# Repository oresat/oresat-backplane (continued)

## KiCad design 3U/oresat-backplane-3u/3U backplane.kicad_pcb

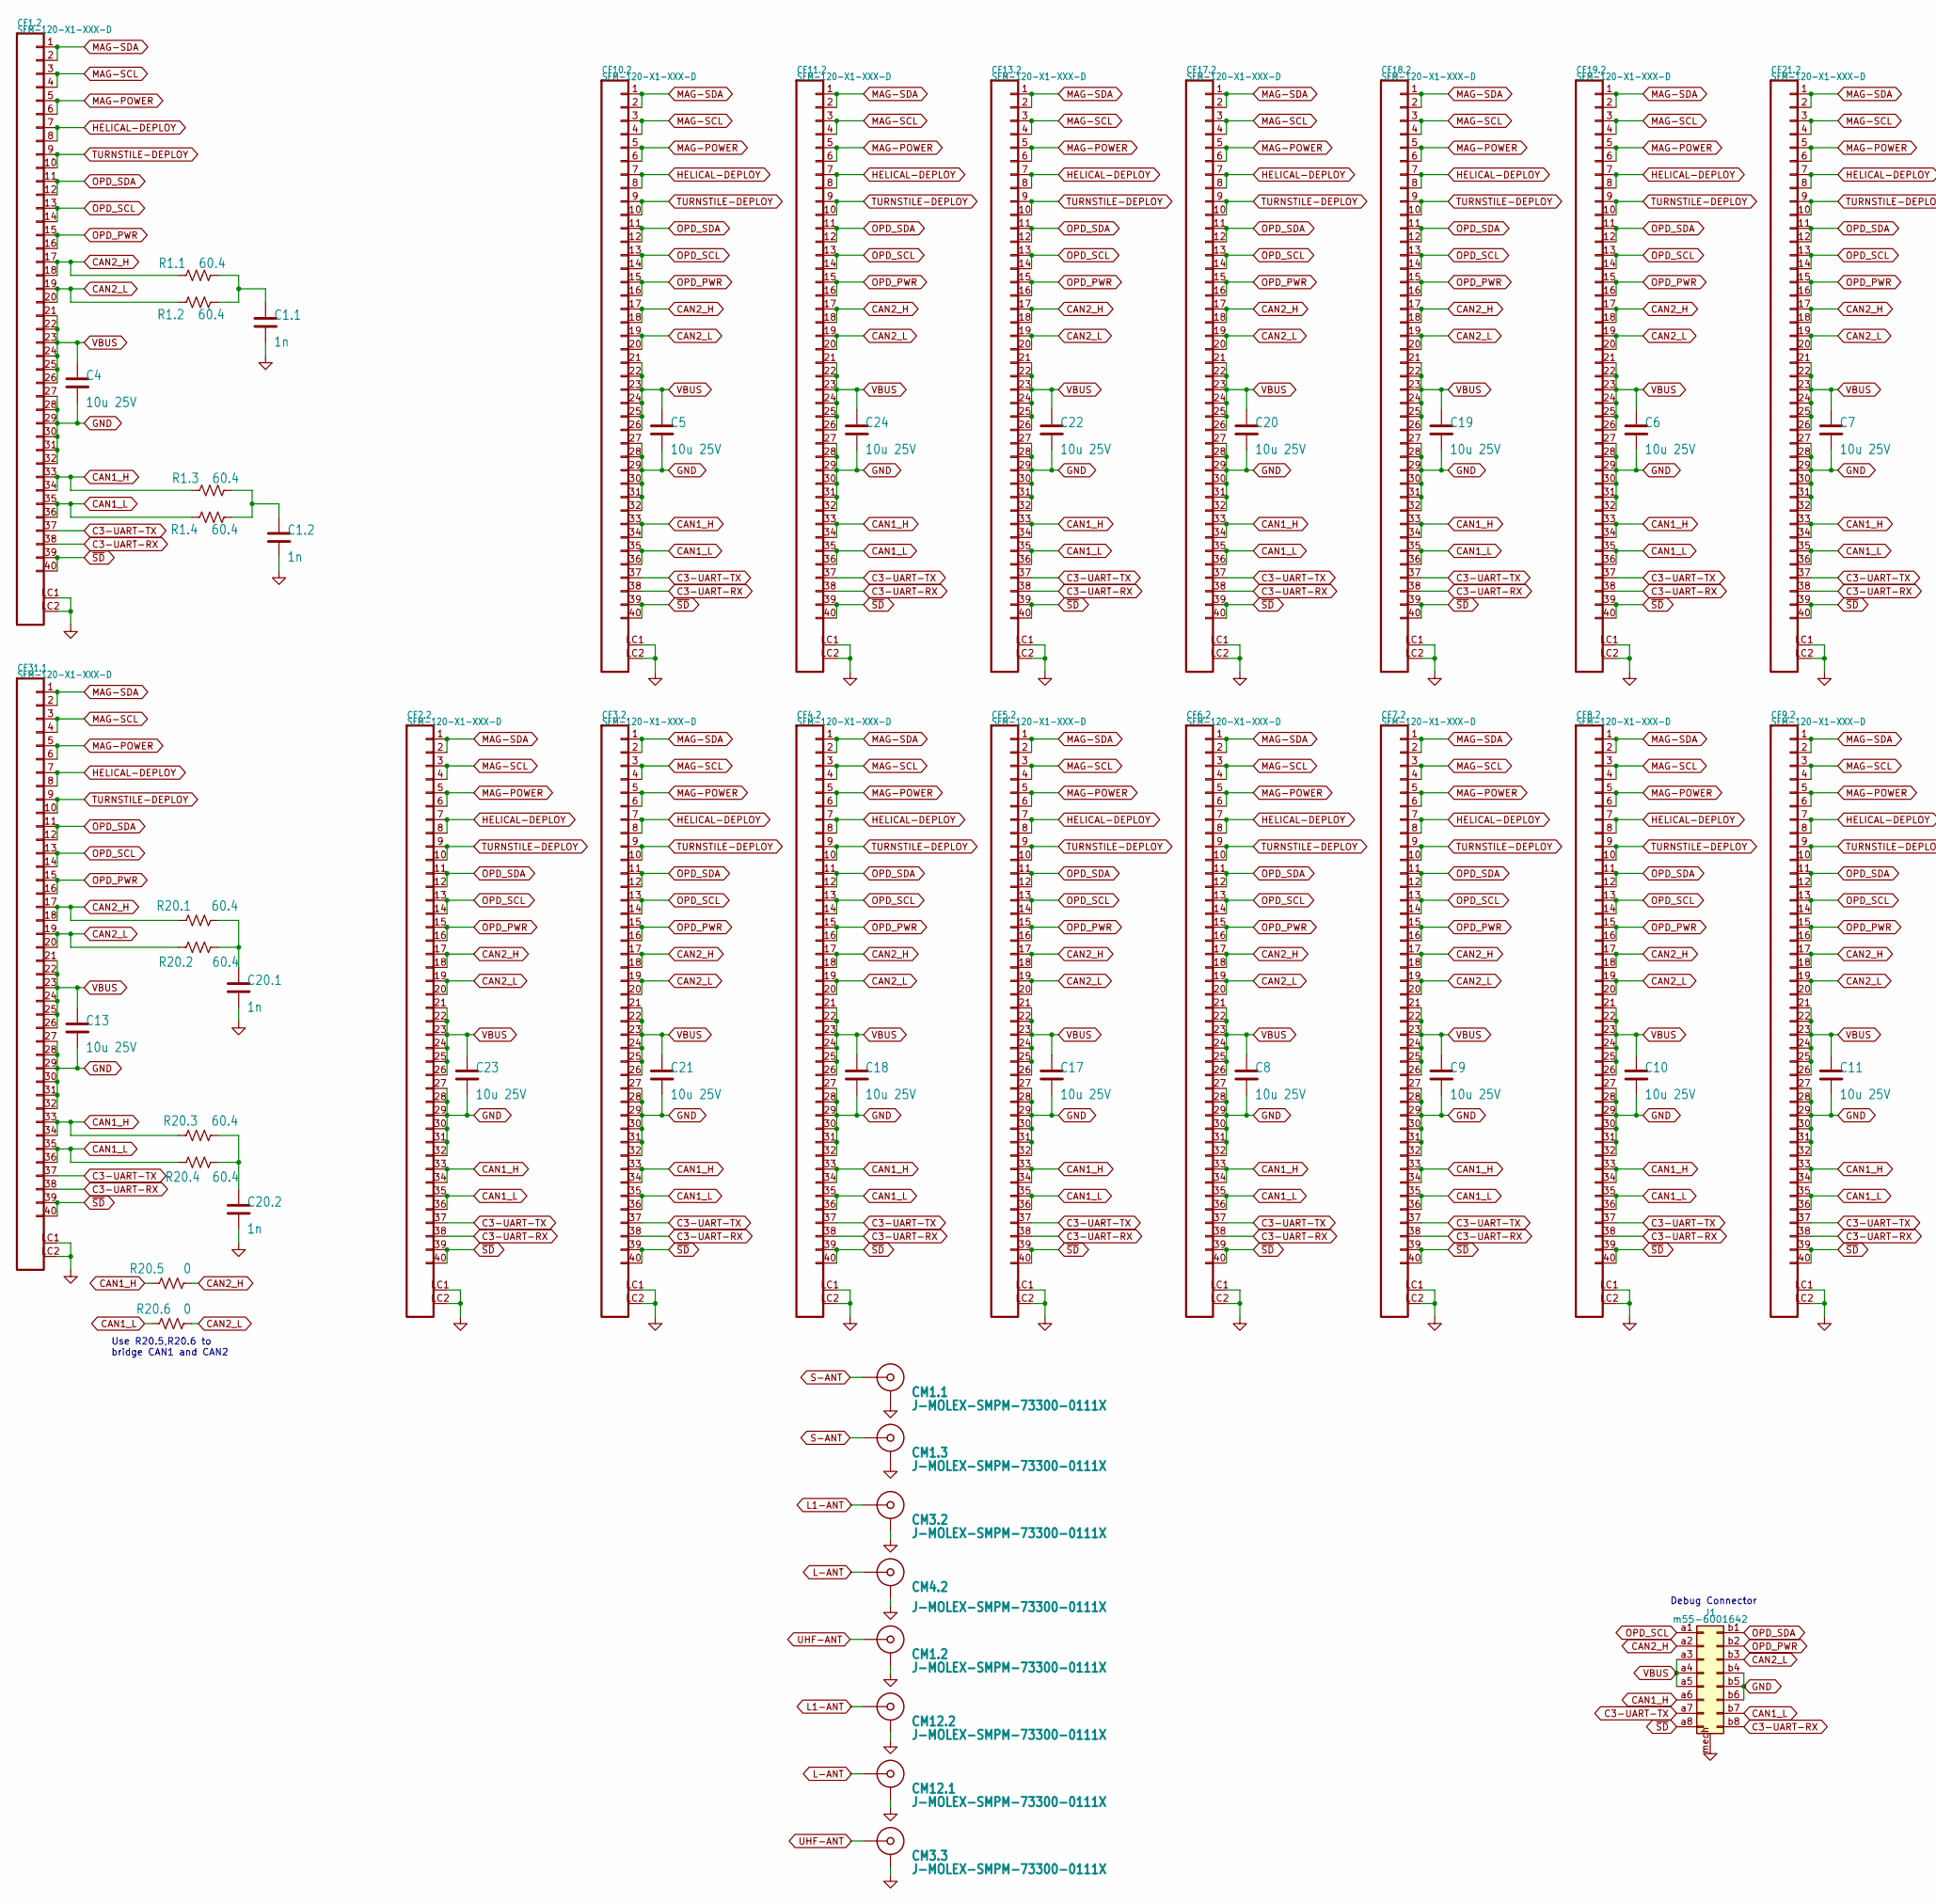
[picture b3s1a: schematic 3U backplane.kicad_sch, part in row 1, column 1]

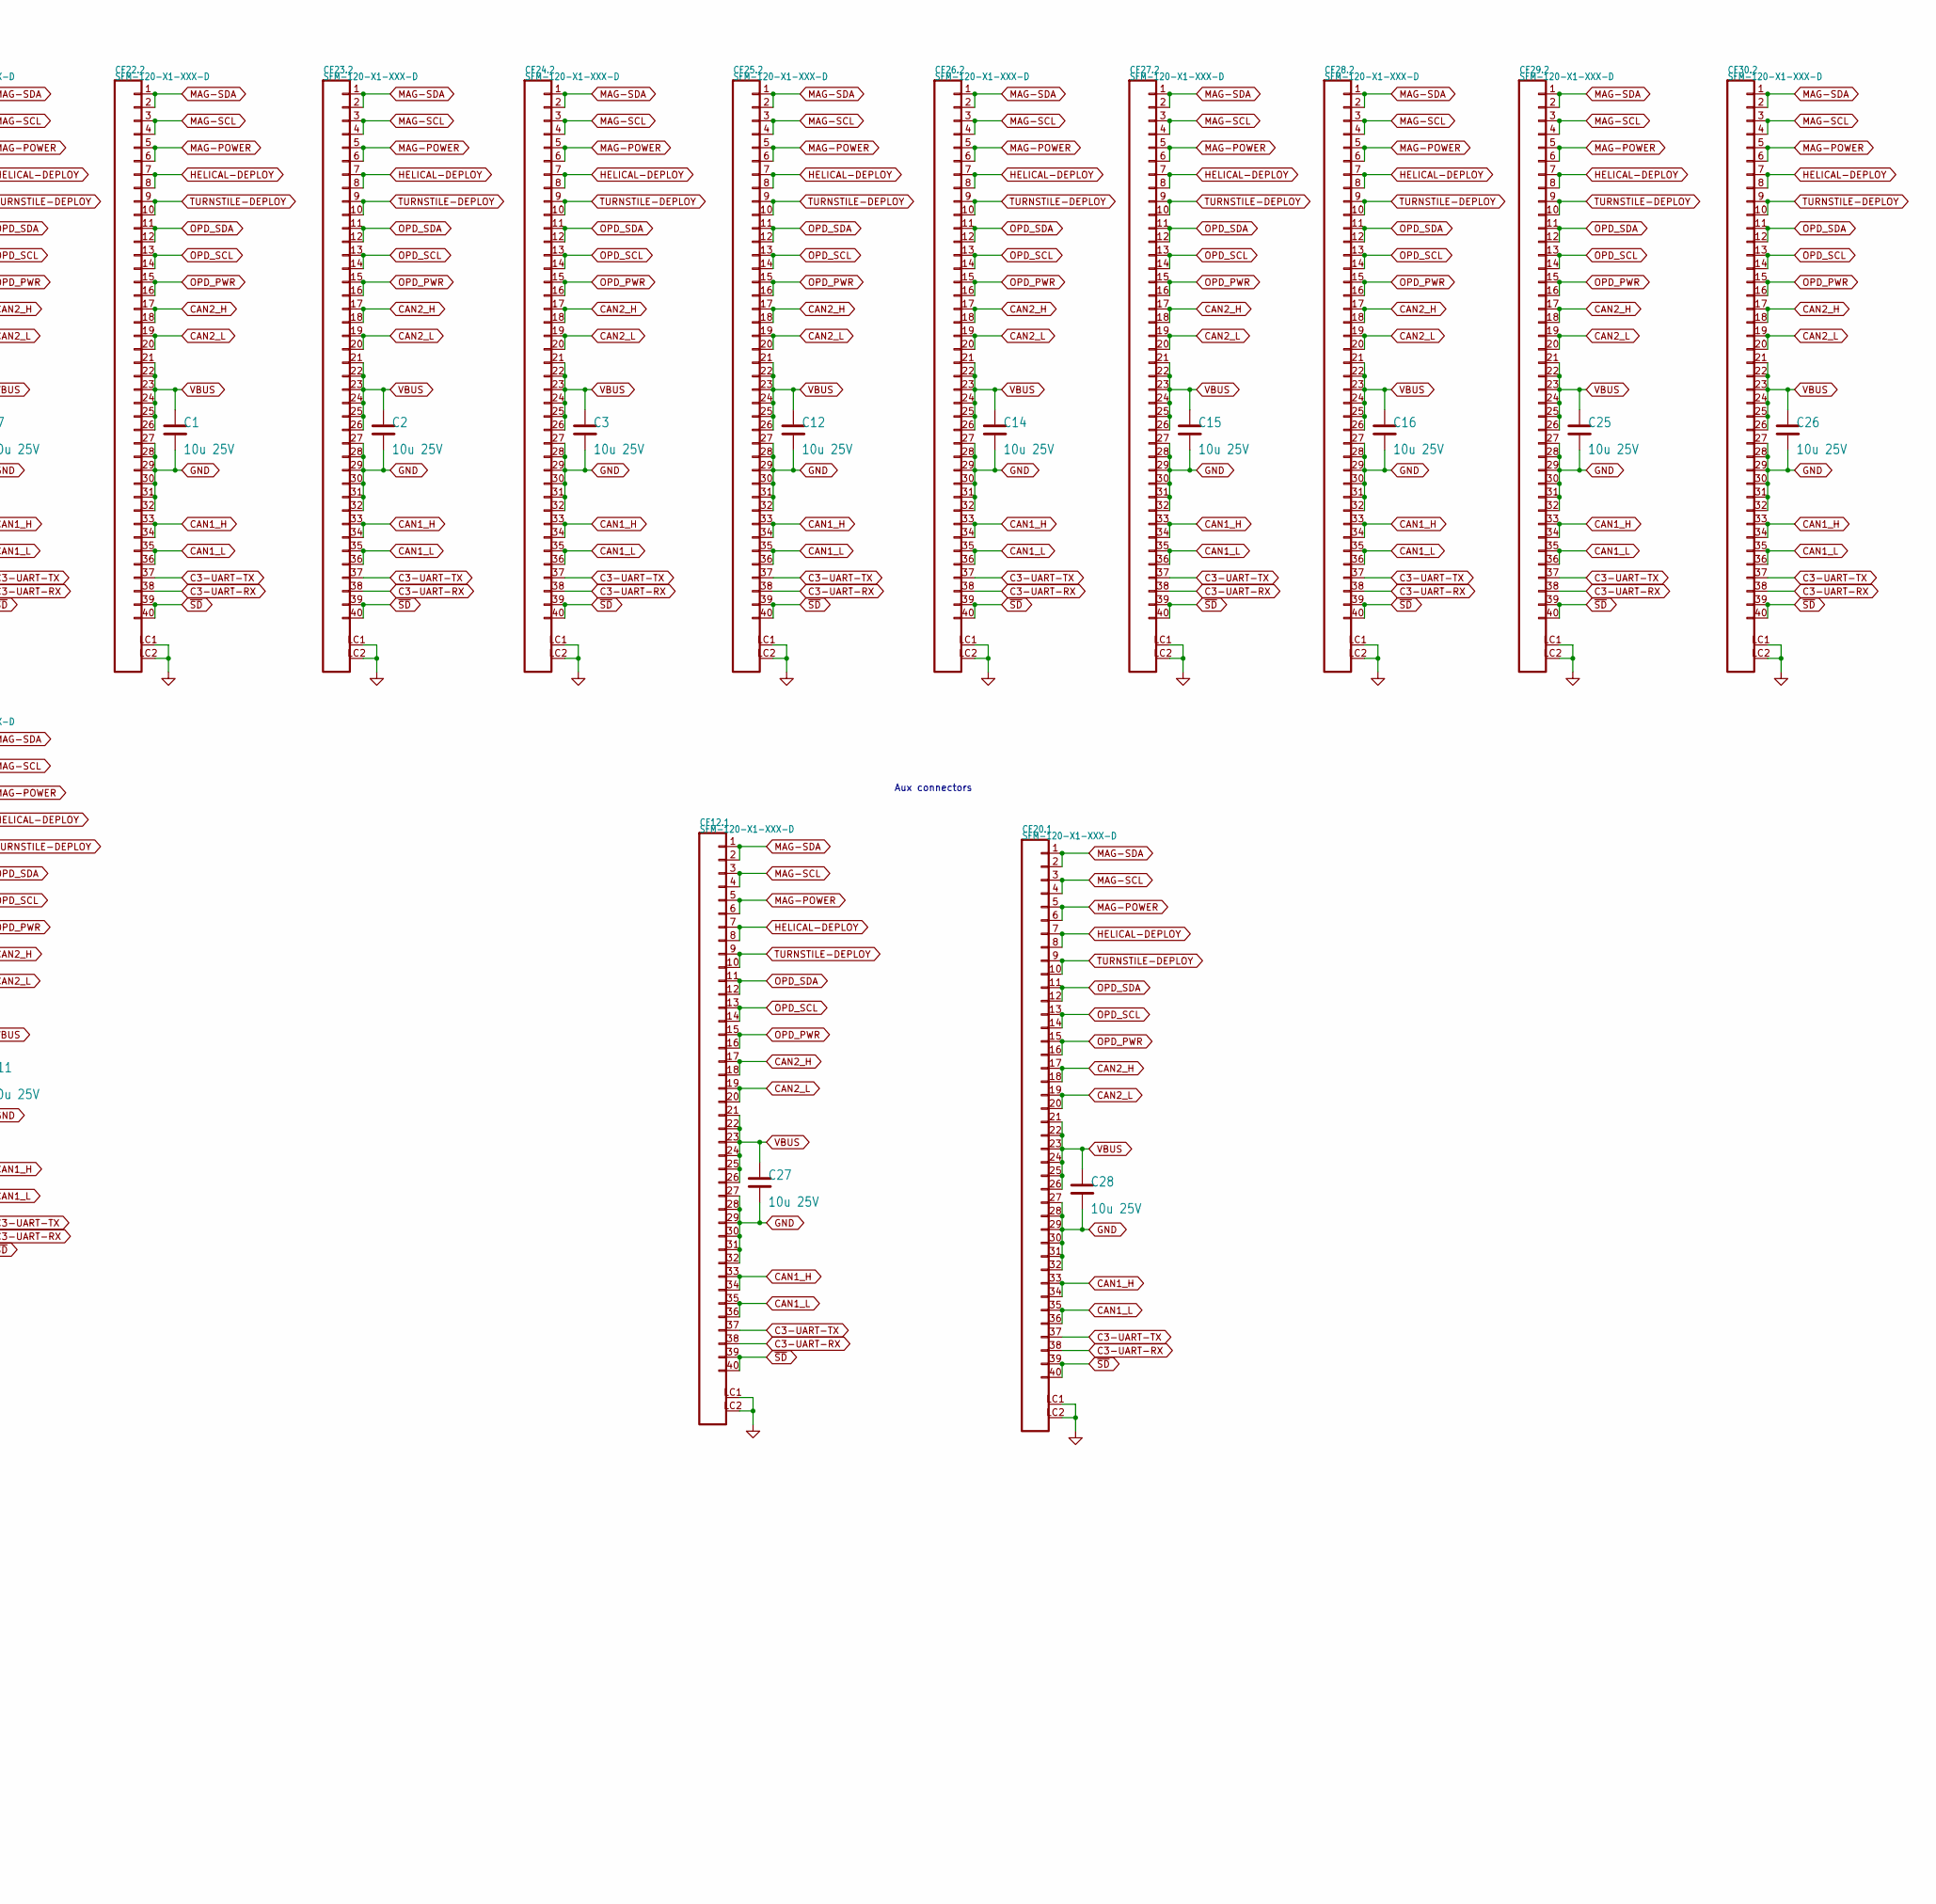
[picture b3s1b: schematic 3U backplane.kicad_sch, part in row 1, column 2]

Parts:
C1, C2, C3, C4, C5, C6, C7, C8, C9, C10, C11, C12, C13, C14, C15, C16, C17, C18, C19, C20, C21, C22, C23, C24, C25, C26, C27, C28: 10u 25V; C_1206_3216Metric
C1.1, C1.2, C20.1, C20.2: 1n; 0603-SMALL
CF1.2, CF2.2, CF3.2, CF4.2, CF5.2, CF6.2, CF7.2, CF8.2, CF9.2, CF10.2, CF11.2, CF12.1, CF13.2, CF17.2, CF18.2, CF19.2, CF20.1, CF21.2, CF22.2, CF23.2, CF24.2, CF25.2, CF26.2, CF27.2, CF28.2, CF29.2, CF30.2, CF31.1: SFM-120-X1-XXX-D; J-SAMTEC-SFM-120-X1-XXX-D
CM1.1, CM1.2, CM1.3, CM3.2, CM3.3, CM4.2, CM12.1, CM12.2: J-MOLEX-SMPM-73300-0111X; J-MOLEX-SMPM-73300-0111X-long
J1: m55-6001642
R1.1, R1.2, R1.3, R1.4, R20.1, R20.2, R20.3, R20.4: 60.4; R_1206_3216Metric
R20.5, R20.6: 0; 0603-SMALL

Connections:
C3-UART-RX: CF1.2.38, CF2.2.38, CF3.2.38, CF4.2.38, CF5.2.38, CF6.2.38, CF7.2.38, CF8.2.38, CF9.2.38, CF10.2.38, CF11.2.38, CF12.1.38, CF13.2.38, CF17.2.38, CF18.2.38, CF19.2.38, CF20.1.38, CF21.2.38, CF22.2.38, CF23.2.38, CF24.2.38, CF25.2.38, CF26.2.38, CF27.2.38, CF28.2.38, CF29.2.38, CF30.2.38, CF31.1.38, J1.b8
C3-UART-TX: CF1.2.37, CF2.2.37, CF3.2.37, CF4.2.37, CF5.2.37, CF6.2.37, CF7.2.37, CF8.2.37, CF9.2.37, CF10.2.37, CF11.2.37, CF12.1.37, CF13.2.37, CF17.2.37, CF18.2.37, CF19.2.37, CF20.1.37, CF21.2.37, CF22.2.37, CF23.2.37, CF24.2.37, CF25.2.37, CF26.2.37, CF27.2.37, CF28.2.37, CF29.2.37, CF30.2.37, CF31.1.37, J1.a7
CAN1_H: CF1.2.33, CF1.2.34, CF2.2.33, CF2.2.34, CF3.2.33, CF3.2.34, CF4.2.33, CF4.2.34, CF5.2.33, CF5.2.34, CF6.2.33, CF6.2.34, CF7.2.33, CF7.2.34, CF8.2.33, CF8.2.34, CF9.2.33, CF9.2.34, CF10.2.33, CF10.2.34, CF11.2.33, CF11.2.34, CF12.1.33, CF12.1.34, CF13.2.33, CF13.2.34, CF17.2.33, CF17.2.34, CF18.2.33, CF18.2.34, CF19.2.33, CF19.2.34, CF20.1.33, CF20.1.34, CF21.2.33, CF21.2.34, CF22.2.33, CF22.2.34, CF23.2.33, CF23.2.34, CF24.2.33, CF24.2.34, CF25.2.33, CF25.2.34, CF26.2.33, CF26.2.34, CF27.2.33, CF27.2.34, CF28.2.33, CF28.2.34, CF29.2.33, CF29.2.34, CF30.2.33, CF30.2.34, CF31.1.33, CF31.1.34, J1.a6, R1.3.2, R20.3.1, R20.5.1
CAN1_L: CF1.2.35, CF1.2.36, CF2.2.35, CF2.2.36, CF3.2.35, CF3.2.36, CF4.2.35, CF4.2.36, CF5.2.35, CF5.2.36, CF6.2.35, CF6.2.36, CF7.2.35, CF7.2.36, CF8.2.35, CF8.2.36, CF9.2.35, CF9.2.36, CF10.2.35, CF10.2.36, CF11.2.35, CF11.2.36, CF12.1.35, CF12.1.36, CF13.2.35, CF13.2.36, CF17.2.35, CF17.2.36, CF18.2.35, CF18.2.36, CF19.2.35, CF19.2.36, CF20.1.35, CF20.1.36, CF21.2.35, CF21.2.36, CF22.2.35, CF22.2.36, CF23.2.35, CF23.2.36, CF24.2.35, CF24.2.36, CF25.2.35, CF25.2.36, CF26.2.35, CF26.2.36, CF27.2.35, CF27.2.36, CF28.2.35, CF28.2.36, CF29.2.35, CF29.2.36, CF30.2.35, CF30.2.36, CF31.1.35, CF31.1.36, J1.b7, R1.4.1, R20.4.2, R20.6.1
CAN2_H: CF1.2.17, CF1.2.18, CF2.2.17, CF2.2.18, CF3.2.17, CF3.2.18, CF4.2.17, CF4.2.18, CF5.2.17, CF5.2.18, CF6.2.17, CF6.2.18, CF7.2.17, CF7.2.18, CF8.2.17, CF8.2.18, CF9.2.17, CF9.2.18, CF10.2.17, CF10.2.18, CF11.2.17, CF11.2.18, CF12.1.17, CF12.1.18, CF13.2.17, CF13.2.18, CF17.2.17, CF17.2.18, CF18.2.17, CF18.2.18, CF19.2.17, CF19.2.18, CF20.1.17, CF20.1.18, CF21.2.17, CF21.2.18, CF22.2.17, CF22.2.18, CF23.2.17, CF23.2.18, CF24.2.17, CF24.2.18, CF25.2.17, CF25.2.18, CF26.2.17, CF26.2.18, CF27.2.17, CF27.2.18, CF28.2.17, CF28.2.18, CF29.2.17, CF29.2.18, CF30.2.17, CF30.2.18, CF31.1.17, CF31.1.18, J1.a2, R1.1.2, R20.1.1, R20.5.2
CAN2_L: CF1.2.19, CF1.2.20, CF2.2.19, CF2.2.20, CF3.2.19, CF3.2.20, CF4.2.19, CF4.2.20, CF5.2.19, CF5.2.20, CF6.2.19, CF6.2.20, CF7.2.19, CF7.2.20, CF8.2.19, CF8.2.20, CF9.2.19, CF9.2.20, CF10.2.19, CF10.2.20, CF11.2.19, CF11.2.20, CF12.1.19, CF12.1.20, CF13.2.19, CF13.2.20, CF17.2.19, CF17.2.20, CF18.2.19, CF18.2.20, CF19.2.19, CF19.2.20, CF20.1.19, CF20.1.20, CF21.2.19, CF21.2.20, CF22.2.19, CF22.2.20, CF23.2.19, CF23.2.20, CF24.2.19, CF24.2.20, CF25.2.19, CF25.2.20, CF26.2.19, CF26.2.20, CF27.2.19, CF27.2.20, CF28.2.19, CF28.2.20, CF29.2.19, CF29.2.20, CF30.2.19, CF30.2.20, CF31.1.19, CF31.1.20, J1.b3, R1.2.1, R20.2.2, R20.6.2
GND: C1.2, C1.1.2, C1.2.2, C2.2, C3.2, C4.2, C5.2, C6.2, C7.2, C8.2, C9.2, C10.2, C11.2, C12.2, C13.2, C14.2, C15.2, C16.2, C17.2, C18.2, C19.2, C20.2, C20.1.2, C20.2.2, C21.2, C22.2, C23.2, C24.2, C25.2, C26.2, C27.2, C28.2, CF1.2.27, CF1.2.28, CF1.2.29, CF1.2.30, CF1.2.31, CF1.2.32, CF1.2.LC1, CF1.2.LC2, CF2.2.27, CF2.2.28, CF2.2.29, CF2.2.30, CF2.2.31, CF2.2.32, CF2.2.LC1, CF2.2.LC2, CF3.2.27, CF3.2.28, CF3.2.29, CF3.2.30, CF3.2.31, CF3.2.32, CF3.2.LC1, CF3.2.LC2, CF4.2.27, CF4.2.28, CF4.2.29, CF4.2.30, CF4.2.31, CF4.2.32, CF4.2.LC1, CF4.2.LC2, CF5.2.27, CF5.2.28, CF5.2.29, CF5.2.30, CF5.2.31, CF5.2.32, CF5.2.LC1, CF5.2.LC2, CF6.2.27, CF6.2.28, CF6.2.29, CF6.2.30, CF6.2.31, CF6.2.32, CF6.2.LC1, CF6.2.LC2, CF7.2.27, CF7.2.28, CF7.2.29, CF7.2.30, CF7.2.31, CF7.2.32, CF7.2.LC1, CF7.2.LC2, CF8.2.27, CF8.2.28, CF8.2.29, CF8.2.30, CF8.2.31, CF8.2.32, CF8.2.LC1, CF8.2.LC2, CF9.2.27, CF9.2.28, CF9.2.29, CF9.2.30, CF9.2.31, CF9.2.32, CF9.2.LC1, CF9.2.LC2, CF10.2.27, CF10.2.28, CF10.2.29, CF10.2.30, CF10.2.31, CF10.2.32, CF10.2.LC1, CF10.2.LC2, CF11.2.27, CF11.2.28, CF11.2.29, CF11.2.30, CF11.2.31, CF11.2.32, CF11.2.LC1, CF11.2.LC2, CF12.1.27, CF12.1.28, CF12.1.29, CF12.1.30, CF12.1.31, CF12.1.32, CF12.1.LC1, CF12.1.LC2, CF13.2.27, CF13.2.28, CF13.2.29, CF13.2.30, CF13.2.31, CF13.2.32, CF13.2.LC1, CF13.2.LC2, CF17.2.27, CF17.2.28, CF17.2.29, CF17.2.30, CF17.2.31, CF17.2.32, CF17.2.LC1, CF17.2.LC2, CF18.2.27, CF18.2.28, CF18.2.29, CF18.2.30, CF18.2.31, CF18.2.32, CF18.2.LC1, CF18.2.LC2, CF19.2.27, CF19.2.28, CF19.2.29, CF19.2.30, CF19.2.31, CF19.2.32, CF19.2.LC1, CF19.2.LC2, CF20.1.27, CF20.1.28, CF20.1.29, CF20.1.30, CF20.1.31, CF20.1.32, CF20.1.LC1, CF20.1.LC2, CF21.2.27, CF21.2.28, CF21.2.29, CF21.2.30, CF21.2.31, CF21.2.32, CF21.2.LC1, CF21.2.LC2, CF22.2.27, CF22.2.28, CF22.2.29, CF22.2.30, CF22.2.31, CF22.2.32, CF22.2.LC1, CF22.2.LC2, CF23.2.27, CF23.2.28, CF23.2.29, CF23.2.30, CF23.2.31, CF23.2.32, CF23.2.LC1, CF23.2.LC2, CF24.2.27, CF24.2.28, CF24.2.29, CF24.2.30, CF24.2.31, CF24.2.32, CF24.2.LC1, CF24.2.LC2, CF25.2.27, CF25.2.28, CF25.2.29, CF25.2.30, CF25.2.31, CF25.2.32, CF25.2.LC1, CF25.2.LC2, CF26.2.27, CF26.2.28, CF26.2.29, CF26.2.30, CF26.2.31, CF26.2.32, CF26.2.LC1, CF26.2.LC2, CF27.2.27, CF27.2.28, CF27.2.29, CF27.2.30, CF27.2.31, CF27.2.32, CF27.2.LC1, CF27.2.LC2, CF28.2.27, CF28.2.28, CF28.2.29, CF28.2.30, CF28.2.31, CF28.2.32, CF28.2.LC1, CF28.2.LC2, CF29.2.27, CF29.2.28, CF29.2.29, CF29.2.30, CF29.2.31, CF29.2.32, CF29.2.LC1, CF29.2.LC2, CF30.2.27, CF30.2.28, CF30.2.29, CF30.2.30, CF30.2.31, CF30.2.32, CF30.2.LC1, CF30.2.LC2, CF31.1.27, CF31.1.28, CF31.1.29, CF31.1.30, CF31.1.31, CF31.1.32, CF31.1.LC1, CF31.1.LC2, CM1.1.GND (SHIELD1), CM1.2.GND (SHIELD1), CM1.3.GND (SHIELD1), CM3.2.GND (SHIELD1), CM3.3.GND (SHIELD1), CM4.2.GND (SHIELD1), CM12.1.GND (SHIELD1), CM12.2.GND (SHIELD1), J1.b4, J1.b5, J1.b6, J1.mech
HELICAL-DEPLOY: CF1.2.7, CF1.2.8, CF2.2.7, CF2.2.8, CF3.2.7, CF3.2.8, CF4.2.7, CF4.2.8, CF5.2.7, CF5.2.8, CF6.2.7, CF6.2.8, CF7.2.7, CF7.2.8, CF8.2.7, CF8.2.8, CF9.2.7, CF9.2.8, CF10.2.7, CF10.2.8, CF11.2.7, CF11.2.8, CF12.1.7, CF12.1.8, CF13.2.7, CF13.2.8, CF17.2.7, CF17.2.8, CF18.2.7, CF18.2.8, CF19.2.7, CF19.2.8, CF20.1.7, CF20.1.8, CF21.2.7, CF21.2.8, CF22.2.7, CF22.2.8, CF23.2.7, CF23.2.8, CF24.2.7, CF24.2.8, CF25.2.7, CF25.2.8, CF26.2.7, CF26.2.8, CF27.2.7, CF27.2.8, CF28.2.7, CF28.2.8, CF29.2.7, CF29.2.8, CF30.2.7, CF30.2.8, CF31.1.7, CF31.1.8
L1-ANT: CM3.2.RF-DOWN (RF), CM12.2.RF-DOWN (RF)
L-ANT: CM4.2.RF-DOWN (RF), CM12.1.RF-DOWN (RF)
MAG-POWER: CF1.2.5, CF1.2.6, CF2.2.5, CF2.2.6, CF3.2.5, CF3.2.6, CF4.2.5, CF4.2.6, CF5.2.5, CF5.2.6, CF6.2.5, CF6.2.6, CF7.2.5, CF7.2.6, CF8.2.5, CF8.2.6, CF9.2.5, CF9.2.6, CF10.2.5, CF10.2.6, CF11.2.5, CF11.2.6, CF12.1.5, CF12.1.6, CF13.2.5, CF13.2.6, CF17.2.5, CF17.2.6, CF18.2.5, CF18.2.6, CF19.2.5, CF19.2.6, CF20.1.5, CF20.1.6, CF21.2.5, CF21.2.6, CF22.2.5, CF22.2.6, CF23.2.5, CF23.2.6, CF24.2.5, CF24.2.6, CF25.2.5, CF25.2.6, CF26.2.5, CF26.2.6, CF27.2.5, CF27.2.6, CF28.2.5, CF28.2.6, CF29.2.5, CF29.2.6, CF30.2.5, CF30.2.6, CF31.1.5, CF31.1.6
MAG-SCL: CF1.2.3, CF1.2.4, CF2.2.3, CF2.2.4, CF3.2.3, CF3.2.4, CF4.2.3, CF4.2.4, CF5.2.3, CF5.2.4, CF6.2.3, CF6.2.4, CF7.2.3, CF7.2.4, CF8.2.3, CF8.2.4, CF9.2.3, CF9.2.4, CF10.2.3, CF10.2.4, CF11.2.3, CF11.2.4, CF12.1.3, CF12.1.4, CF13.2.3, CF13.2.4, CF17.2.3, CF17.2.4, CF18.2.3, CF18.2.4, CF19.2.3, CF19.2.4, CF20.1.3, CF20.1.4, CF21.2.3, CF21.2.4, CF22.2.3, CF22.2.4, CF23.2.3, CF23.2.4, CF24.2.3, CF24.2.4, CF25.2.3, CF25.2.4, CF26.2.3, CF26.2.4, CF27.2.3, CF27.2.4, CF28.2.3, CF28.2.4, CF29.2.3, CF29.2.4, CF30.2.3, CF30.2.4, CF31.1.3, CF31.1.4
MAG-SDA: CF1.2.1, CF1.2.2, CF2.2.1, CF2.2.2, CF3.2.1, CF3.2.2, CF4.2.1, CF4.2.2, CF5.2.1, CF5.2.2, CF6.2.1, CF6.2.2, CF7.2.1, CF7.2.2, CF8.2.1, CF8.2.2, CF9.2.1, CF9.2.2, CF10.2.1, CF10.2.2, CF11.2.1, CF11.2.2, CF12.1.1, CF12.1.2, CF13.2.1, CF13.2.2, CF17.2.1, CF17.2.2, CF18.2.1, CF18.2.2, CF19.2.1, CF19.2.2, CF20.1.1, CF20.1.2, CF21.2.1, CF21.2.2, CF22.2.1, CF22.2.2, CF23.2.1, CF23.2.2, CF24.2.1, CF24.2.2, CF25.2.1, CF25.2.2, CF26.2.1, CF26.2.2, CF27.2.1, CF27.2.2, CF28.2.1, CF28.2.2, CF29.2.1, CF29.2.2, CF30.2.1, CF30.2.2, CF31.1.1, CF31.1.2
unnamed: C1.1.1, R1.1.1, R1.2.2
unnamed: C1.2.1, R1.3.1, R1.4.2
unnamed: C20.1.1, R20.1.2, R20.2.1
unnamed: C20.2.1, R20.3.2, R20.4.1
OPD_PWR: CF1.2.15, CF1.2.16, CF2.2.15, CF2.2.16, CF3.2.15, CF3.2.16, CF4.2.15, CF4.2.16, CF5.2.15, CF5.2.16, CF6.2.15, CF6.2.16, CF7.2.15, CF7.2.16, CF8.2.15, CF8.2.16, CF9.2.15, CF9.2.16, CF10.2.15, CF10.2.16, CF11.2.15, CF11.2.16, CF12.1.15, CF12.1.16, CF13.2.15, CF13.2.16, CF17.2.15, CF17.2.16, CF18.2.15, CF18.2.16, CF19.2.15, CF19.2.16, CF20.1.15, CF20.1.16, CF21.2.15, CF21.2.16, CF22.2.15, CF22.2.16, CF23.2.15, CF23.2.16, CF24.2.15, CF24.2.16, CF25.2.15, CF25.2.16, CF26.2.15, CF26.2.16, CF27.2.15, CF27.2.16, CF28.2.15, CF28.2.16, CF29.2.15, CF29.2.16, CF30.2.15, CF30.2.16, CF31.1.15, CF31.1.16, J1.b2
OPD_SCL: CF1.2.13, CF1.2.14, CF2.2.13, CF2.2.14, CF3.2.13, CF3.2.14, CF4.2.13, CF4.2.14, CF5.2.13, CF5.2.14, CF6.2.13, CF6.2.14, CF7.2.13, CF7.2.14, CF8.2.13, CF8.2.14, CF9.2.13, CF9.2.14, CF10.2.13, CF10.2.14, CF11.2.13, CF11.2.14, CF12.1.13, CF12.1.14, CF13.2.13, CF13.2.14, CF17.2.13, CF17.2.14, CF18.2.13, CF18.2.14, CF19.2.13, CF19.2.14, CF20.1.13, CF20.1.14, CF21.2.13, CF21.2.14, CF22.2.13, CF22.2.14, CF23.2.13, CF23.2.14, CF24.2.13, CF24.2.14, CF25.2.13, CF25.2.14, CF26.2.13, CF26.2.14, CF27.2.13, CF27.2.14, CF28.2.13, CF28.2.14, CF29.2.13, CF29.2.14, CF30.2.13, CF30.2.14, CF31.1.13, CF31.1.14, J1.a1
OPD_SDA: CF1.2.11, CF1.2.12, CF2.2.11, CF2.2.12, CF3.2.11, CF3.2.12, CF4.2.11, CF4.2.12, CF5.2.11, CF5.2.12, CF6.2.11, CF6.2.12, CF7.2.11, CF7.2.12, CF8.2.11, CF8.2.12, CF9.2.11, CF9.2.12, CF10.2.11, CF10.2.12, CF11.2.11, CF11.2.12, CF12.1.11, CF12.1.12, CF13.2.11, CF13.2.12, CF17.2.11, CF17.2.12, CF18.2.11, CF18.2.12, CF19.2.11, CF19.2.12, CF20.1.11, CF20.1.12, CF21.2.11, CF21.2.12, CF22.2.11, CF22.2.12, CF23.2.11, CF23.2.12, CF24.2.11, CF24.2.12, CF25.2.11, CF25.2.12, CF26.2.11, CF26.2.12, CF27.2.11, CF27.2.12, CF28.2.11, CF28.2.12, CF29.2.11, CF29.2.12, CF30.2.11, CF30.2.12, CF31.1.11, CF31.1.12, J1.b1
S-ANT: CM1.1.RF-DOWN (RF), CM1.3.RF-DOWN (RF)
TURNSTILE-DEPLOY: CF1.2.9, CF1.2.10, CF2.2.9, CF2.2.10, CF3.2.9, CF3.2.10, CF4.2.9, CF4.2.10, CF5.2.9, CF5.2.10, CF6.2.9, CF6.2.10, CF7.2.9, CF7.2.10, CF8.2.9, CF8.2.10, CF9.2.9, CF9.2.10, CF10.2.9, CF10.2.10, CF11.2.9, CF11.2.10, CF12.1.9, CF12.1.10, CF13.2.9, CF13.2.10, CF17.2.9, CF17.2.10, CF18.2.9, CF18.2.10, CF19.2.9, CF19.2.10, CF20.1.9, CF20.1.10, CF21.2.9, CF21.2.10, CF22.2.9, CF22.2.10, CF23.2.9, CF23.2.10, CF24.2.9, CF24.2.10, CF25.2.9, CF25.2.10, CF26.2.9, CF26.2.10, CF27.2.9, CF27.2.10, CF28.2.9, CF28.2.10, CF29.2.9, CF29.2.10, CF30.2.9, CF30.2.10, CF31.1.9, CF31.1.10
UHF-ANT: CM1.2.RF-DOWN (RF), CM3.3.RF-DOWN (RF)
VBUS: C1.1, C2.1, C3.1, C4.1, C5.1, C6.1, C7.1, C8.1, C9.1, C10.1, C11.1, C12.1, C13.1, C14.1, C15.1, C16.1, C17.1, C18.1, C19.1, C20.1, C21.1, C22.1, C23.1, C24.1, C25.1, C26.1, C27.1, C28.1, CF1.2.21, CF1.2.22, CF1.2.23, CF1.2.24, CF1.2.25, CF1.2.26, CF2.2.21, CF2.2.22, CF2.2.23, CF2.2.24, CF2.2.25, CF2.2.26, CF3.2.21, CF3.2.22, CF3.2.23, CF3.2.24, CF3.2.25, CF3.2.26, CF4.2.21, CF4.2.22, CF4.2.23, CF4.2.24, CF4.2.25, CF4.2.26, CF5.2.21, CF5.2.22, CF5.2.23, CF5.2.24, CF5.2.25, CF5.2.26, CF6.2.21, CF6.2.22, CF6.2.23, CF6.2.24, CF6.2.25, CF6.2.26, CF7.2.21, CF7.2.22, CF7.2.23, CF7.2.24, CF7.2.25, CF7.2.26, CF8.2.21, CF8.2.22, CF8.2.23, CF8.2.24, CF8.2.25, CF8.2.26, CF9.2.21, CF9.2.22, CF9.2.23, CF9.2.24, CF9.2.25, CF9.2.26, CF10.2.21, CF10.2.22, CF10.2.23, CF10.2.24, CF10.2.25, CF10.2.26, CF11.2.21, CF11.2.22, CF11.2.23, CF11.2.24, CF11.2.25, CF11.2.26, CF12.1.21, CF12.1.22, CF12.1.23, CF12.1.24, CF12.1.25, CF12.1.26, CF13.2.21, CF13.2.22, CF13.2.23, CF13.2.24, CF13.2.25, CF13.2.26, CF17.2.21, CF17.2.22, CF17.2.23, CF17.2.24, CF17.2.25, CF17.2.26, CF18.2.21, CF18.2.22, CF18.2.23, CF18.2.24, CF18.2.25, CF18.2.26, CF19.2.21, CF19.2.22, CF19.2.23, CF19.2.24, CF19.2.25, CF19.2.26, CF20.1.21, CF20.1.22, CF20.1.23, CF20.1.24, CF20.1.25, CF20.1.26, CF21.2.21, CF21.2.22, CF21.2.23, CF21.2.24, CF21.2.25, CF21.2.26, CF22.2.21, CF22.2.22, CF22.2.23, CF22.2.24, CF22.2.25, CF22.2.26, CF23.2.21, CF23.2.22, CF23.2.23, CF23.2.24, CF23.2.25, CF23.2.26, CF24.2.21, CF24.2.22, CF24.2.23, CF24.2.24, CF24.2.25, CF24.2.26, CF25.2.21, CF25.2.22, CF25.2.23, CF25.2.24, CF25.2.25, CF25.2.26, CF26.2.21, CF26.2.22, CF26.2.23, CF26.2.24, CF26.2.25, CF26.2.26, CF27.2.21, CF27.2.22, CF27.2.23, CF27.2.24, CF27.2.25, CF27.2.26, CF28.2.21, CF28.2.22, CF28.2.23, CF28.2.24, CF28.2.25, CF28.2.26, CF29.2.21, CF29.2.22, CF29.2.23, CF29.2.24, CF29.2.25, CF29.2.26, CF30.2.21, CF30.2.22, CF30.2.23, CF30.2.24, CF30.2.25, CF30.2.26, CF31.1.21, CF31.1.22, CF31.1.23, CF31.1.24, CF31.1.25, CF31.1.26, J1.a3, J1.a4, J1.a5
~SD: CF1.2.39, CF1.2.40, CF2.2.39, CF2.2.40, CF3.2.39, CF3.2.40, CF4.2.39, CF4.2.40, CF5.2.39, CF5.2.40, CF6.2.39, CF6.2.40, CF7.2.39, CF7.2.40, CF8.2.39, CF8.2.40, CF9.2.39, CF9.2.40, CF10.2.39, CF10.2.40, CF11.2.39, CF11.2.40, CF12.1.39, CF12.1.40, CF13.2.39, CF13.2.40, CF17.2.39, CF17.2.40, CF18.2.39, CF18.2.40, CF19.2.39, CF19.2.40, CF20.1.39, CF20.1.40, CF21.2.39, CF21.2.40, CF22.2.39, CF22.2.40, CF23.2.39, CF23.2.40, CF24.2.39, CF24.2.40, CF25.2.39, CF25.2.40, CF26.2.39, CF26.2.40, CF27.2.39, CF27.2.40, CF28.2.39, CF28.2.40, CF29.2.39, CF29.2.40, CF30.2.39, CF30.2.40, CF31.1.39, CF31.1.40, J1.a8

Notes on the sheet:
Aux connectors
Debug Connector
Use R20.5,R20.6 to bridge CAN1 and CAN2

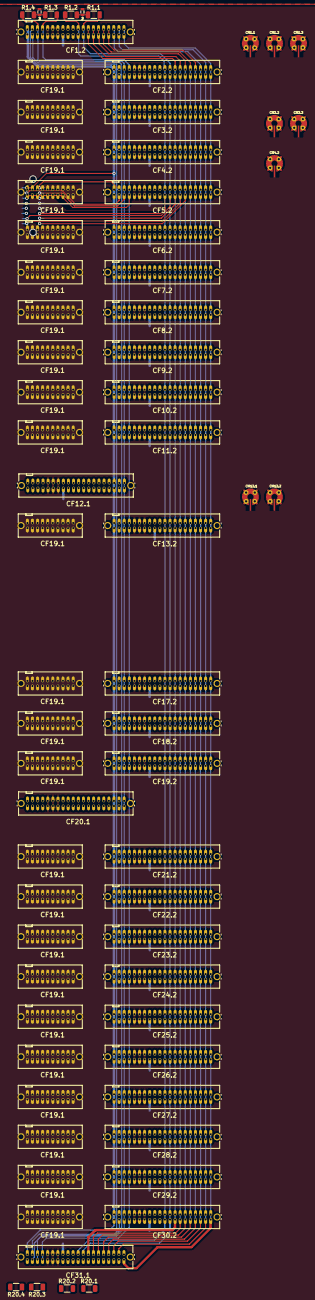
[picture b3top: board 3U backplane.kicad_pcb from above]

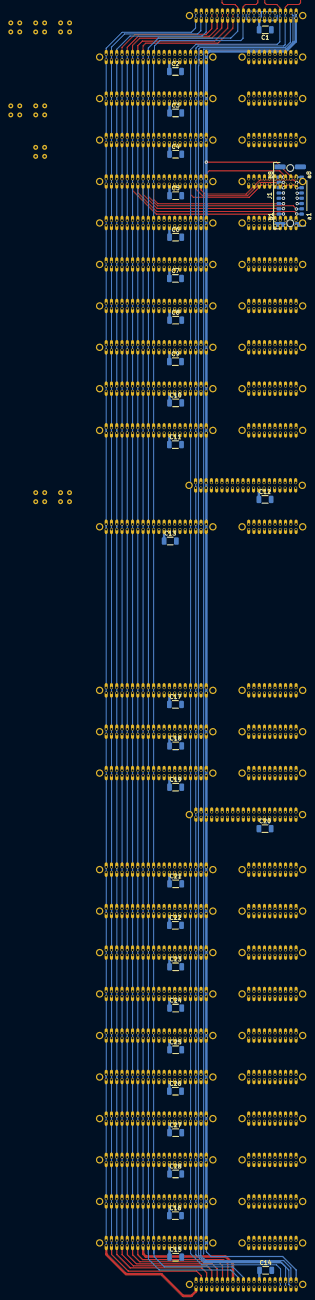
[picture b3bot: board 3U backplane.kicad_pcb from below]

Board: 4 copper layers, 99 parts (29 on the bottom side), 25 nets.

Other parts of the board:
CF19.1, CF19.1#2, CF19.1#3, CF19.1#4, CF19.1#5, CF19.1#6, CF19.1#7, CF19.1#8, CF19.1#9, CF19.1#10, CF19.1#11, CF19.1#12, CF19.1#13, CF19.1#14, CF19.1#15, CF19.1#16, CF19.1#17, CF19.1#18, CF19.1#19, CF19.1#20, CF19.1#21, CF19.1#22, CF19.1#23, CF19.1#24: SFM-110-X1-XXX-D-LC; J-SAMTEC-CF-SFM-110-X1-XXX-D-LC
